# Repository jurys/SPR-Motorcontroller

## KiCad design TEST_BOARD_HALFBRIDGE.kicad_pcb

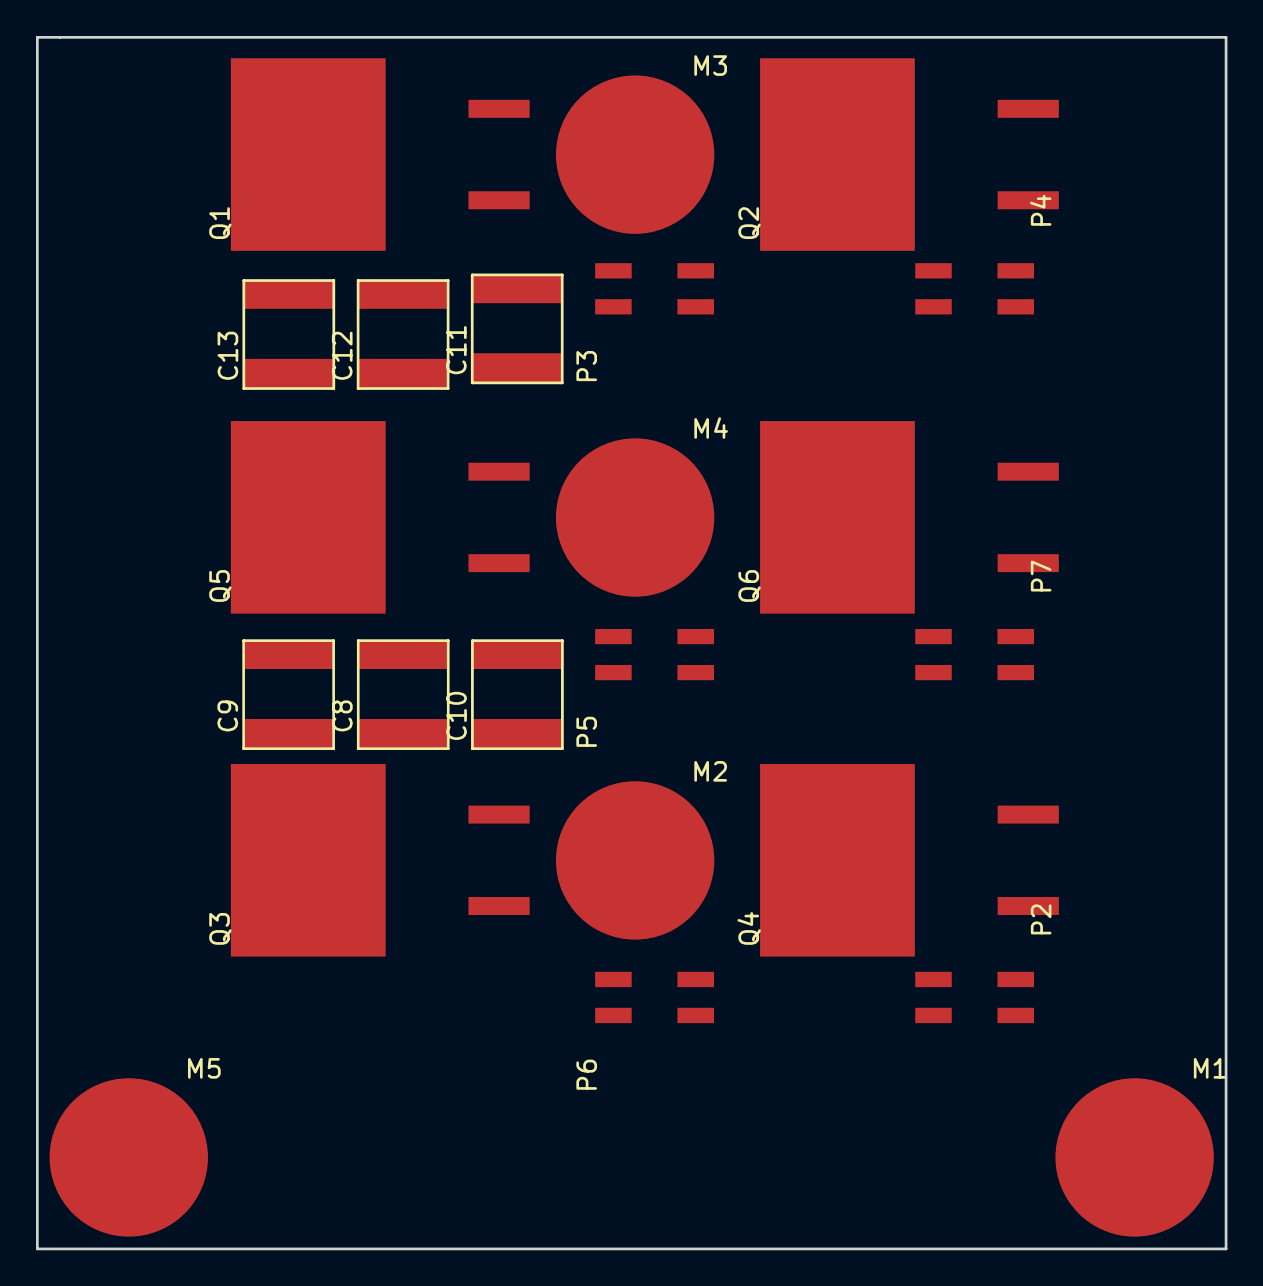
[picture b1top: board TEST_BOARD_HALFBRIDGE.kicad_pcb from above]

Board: 2 copper layers, 66.0 x 67.3 mm, 23 parts (0 on the bottom side), 11 nets, no tracks yet.

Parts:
C8, C9, C10, C11, C12, C13: UCZ1K331MNQ1MS; CKG57
M1, M2, M3, M4, M5: WP-BUFU_M4; WP-SMSH_SMT_Shank_M4
P2, P3, P4, P5, P6, P7: CONN_02X02; WR-PHD_2x2
Q1, Q2, Q3, Q4, Q5, Q6: Q_PMOS_GDS; TO-263

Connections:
GNDPWR: C8.2, C9.2, C10.2, C11.2, C12.2, C13.2, M1.1, Q2.3, Q4.3, Q6.3
unnamed: C8.1, C9.1, C10.1, C11.1, C12.1, C13.1, M5.1, Q1.2, Q3.2, Q5.2
unnamed: M2.1, P6.1, P6.3, Q3.3, Q4.2
unnamed: M3.1, P3.1, P3.3, Q1.3, Q2.2
unnamed: M4.1, P5.1, P5.3, Q5.3, Q6.2
unnamed: P2.1, P2.2, P2.3, P2.4, Q4.1
unnamed: P3.2, P3.4, Q1.1
unnamed: P4.1, P4.2, P4.3, P4.4, Q2.1
unnamed: P5.2, P5.4, Q5.1
unnamed: P6.2, P6.4, Q3.1
unnamed: P7.1, P7.2, P7.3, P7.4, Q6.1

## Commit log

2016-02-29 new repository
